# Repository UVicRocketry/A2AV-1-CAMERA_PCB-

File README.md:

PCB for controlling and powering camera onboard anduril 2

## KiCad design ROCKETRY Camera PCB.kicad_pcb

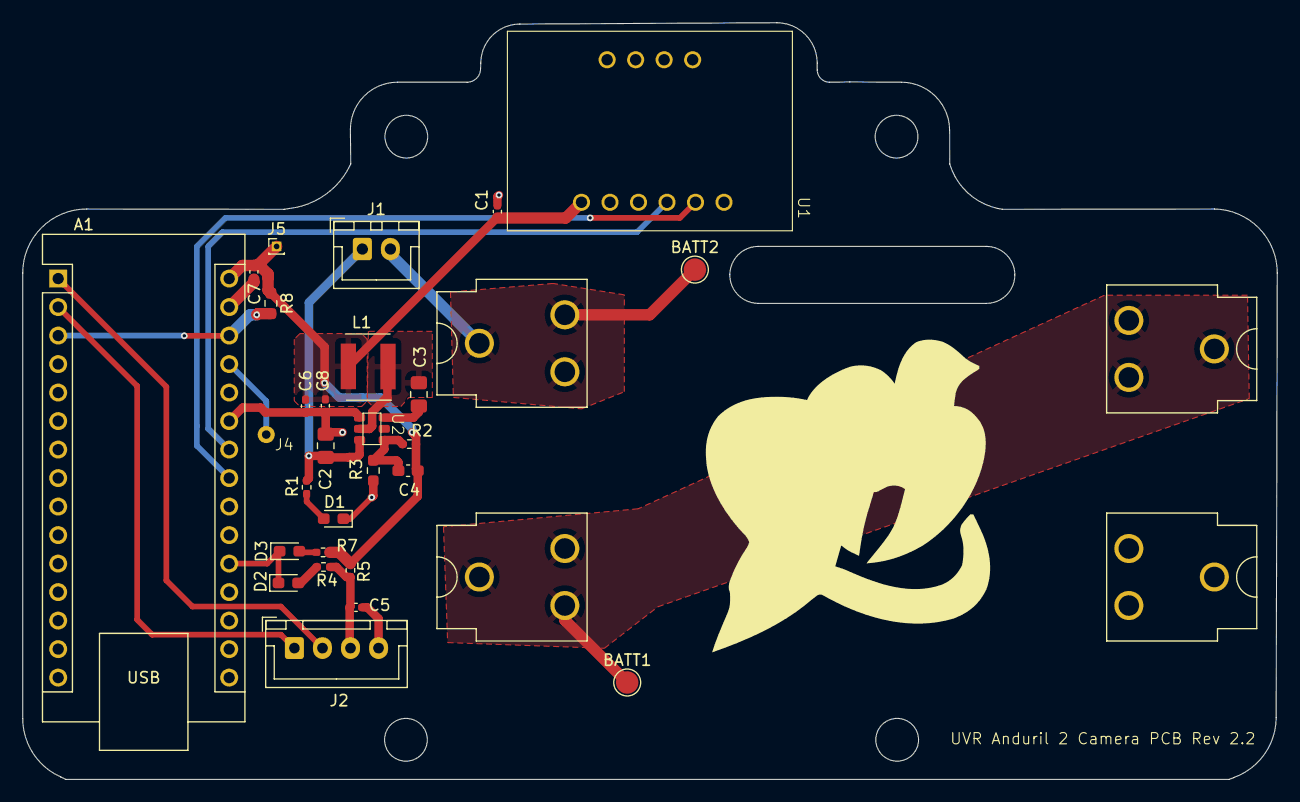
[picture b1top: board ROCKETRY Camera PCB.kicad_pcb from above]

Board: 2 copper layers, 111.8 x 67.4 mm, 30 parts (0 on the bottom side), 18 nets.

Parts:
A1: Arduino_Nano_v2.x; Arduino_Nano
BATT1, BATT2: TestPoint; TestPoint_Pad_D2.0mm
BT1, BT2: 3.6V; BatteryClip_Keystone_54_D16-19mm
C1, C5, C7: 100nF; C_0402_1005Metric_Pad0.74x0.62mm_HandSolder
C2: 10uF; C_0805_2012Metric_Pad1.18x1.45mm_HandSolder
C3: 330nF; C_0805_2012Metric_Pad1.18x1.45mm_HandSolder
C4: 100pF; C_0603_1608Metric_Pad1.08x0.95mm_HandSolder
C6, C8: 22uF; C_0402_1005Metric_Pad0.74x0.62mm_HandSolder
D1, D2, D3: LED; LED_0603_1608Metric_Pad1.05x0.95mm_HandSolder
J1: Conn_01x02_Pin; JST_XH_B2B-XH-A_1x02_P2.50mm_Vertical
J2: Conn_01x03_Pin; JST_XH_B4B-XH-A_1x04_P2.50mm_Vertical
J4: Conn_01x01_Pin; mouonting_hole
J5: Conn_01x01_Pin; PinHeader_1x01_P1.00mm_Vertical
L1: 4.7uH; BOURNS_SRN5040_CUSTOM
R1, R4, R7: 1k; R_0402_1005Metric_Pad0.72x0.64mm_HandSolder
R2: 52.3k; R_0402_1005Metric_Pad0.72x0.64mm_HandSolder
R3, R8: 10k; R_0603_1608Metric_Pad0.98x0.95mm_HandSolder
R5: 0; R_0402_1005Metric_Pad0.72x0.64mm_HandSolder
U1: ADX375L
U2: AP62200WU; TSOT26

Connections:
+5V: A1.30 (VIN), C1.1, C4.1, C6.1, C7.2, C8.1, J5.1, L1.2, R2.1, R5.1, R7.1, R8.1, U1.5 (VIN)
+BATT: BATT1.1, BT1.2 (-), BT2.1 (+)
/SCL: A1.24 (A5), U1.7 (SCL)
/SDA: A1.23 (A4), U1.8 (SDA)
GND: A1.4 (GND), A1.5 (D2), A1.6 (D3), A1.7 (D4), A1.8 (D5), A1.9 (D6), A1.10 (D7), A1.11 (D8), A1.12 (D9), A1.13 (D10), A1.14 (D11), A1.15 (D12), A1.16 (D13), A1.18 (AREF), A1.19 (A0), A1.20 (A1), A1.21 (A2), A1.22 (A3), A1.25 (A6), A1.26 (A7), A1.29 (GND), BT2.2 (-), C1.2, C2.2, C5.2, C6.2, C7.1, C8.2, D1.1 (K), D2.1 (K), D3.1 (K), J2.4, R3.2, U1.1 (GND), U1.2 (I2), U1.3 (SNO), U1.4 (CS), U1.6 (GND), U1.9 (INT), U2.1 (GND)
unnamed: A1.27 (+5V), J4.1
unnamed: A1.2 (D0/RX), J2.1
unnamed: A1.1 (D1/TX), J2.2
unnamed: A1.3 (~RESET), A1.28 (~RESET), R8.2
unnamed: D1.2 (A), R1.2
unnamed: D2.2 (A), R4.2
unnamed: D3.2 (A), R7.2
unnamed: C2.1, J1.1, R1.1, U2.3 (VIN)
unnamed: C5.1, J2.3, R4.1, R5.2
unnamed: C3.2, U2.6 (BST)
unnamed: C4.2, R2.2, R3.1, U2.4 (FB)
unnamed: C3.1, L1.1, U2.2 (SW)
VCC: BATT2.1, BT1.1 (+), J1.2

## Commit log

2024-12-14 Plotted Pdfs
2024-12-14 Rocket ID now accurate
2025-01-02 First commit after import to UVR
2025-01-02 aligned holes
2025-01-18 exported step
2025-01-18 clean up autosaves
2025-01-18 remove redundant stp
2025-02-09 swapped tht components with smt, in progress of routing traces. Board will be waaaaay cleaner
2025-02-12 pcb ready for final review/ ordering
2025-02-16 adding curves to pcb edges
2025-02-16 added curves to pcb edges, added connector for screw switch
2025-02-16 reexport step properly
2025-02-27 made critical updates based on Aila's feedback
2025-03-01 finished with updates, has my approval to order
2025-03-01 the board was a bit deformed. it should be better now
2025-03-01 more deformities fixed
2025-03-08 final touches before exporting gerbers
2025-03-08 exported gerbers
2025-07-13 clean up schematic for the report
2025-07-13 fix small connection mistake
2025-07-19 add mounting hole dimension
